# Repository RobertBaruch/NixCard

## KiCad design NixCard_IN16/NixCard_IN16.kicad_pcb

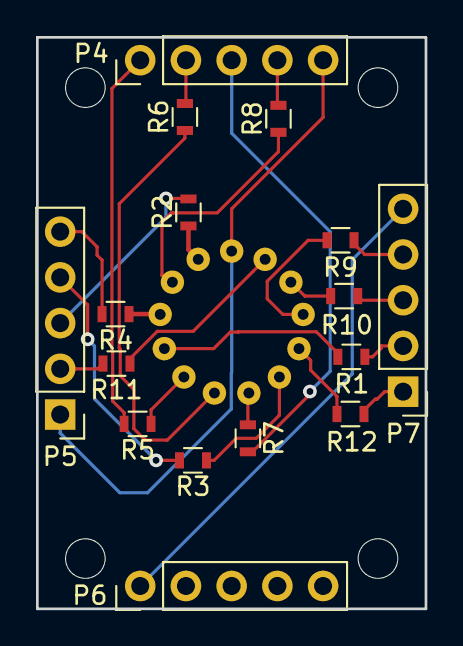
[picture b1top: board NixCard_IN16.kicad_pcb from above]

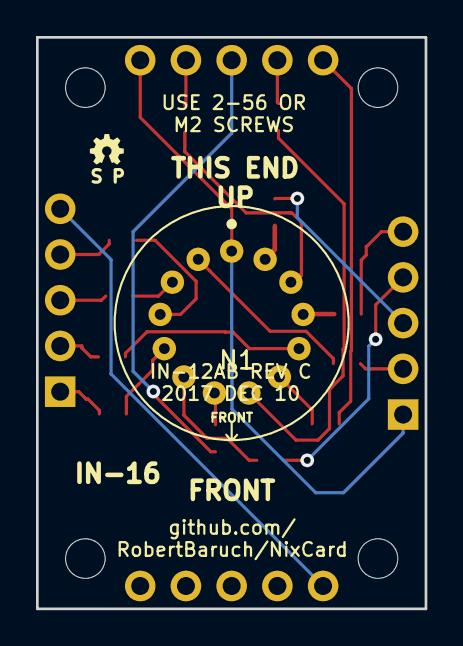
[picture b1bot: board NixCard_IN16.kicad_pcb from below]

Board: 2 copper layers, 21.6 x 31.8 mm, 18 parts (2 on the bottom side), 26 nets.

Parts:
N1: IN-16; IN-16-skt
P4, P5, P6, P7: CONN_01X05; Pin_Header_Straight_1x05_Pitch2.54mm
R1, R12: 120k; R_0603
R2, R3, R4, R5, R6, R7, R8, R9, R10, R11: 20k; R_0603
svg2mod: G***; oshw-logo-gear

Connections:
/HV0: P5.2, R11.2
/HV1: P5.3, R2.2
/HV2: P5.4, R3.2
/HV3: P5.5, R4.2
/HV4: P4.1, R5.2
/HV5: P4.2, R6.2
/HV6: P4.3, R7.2
/HV7: P4.4, R8.2
/HV8: P7.4, R9.2
/HV9: P7.3, R10.2
/HV10: P7.2, R1.2
/HV11: P7.1, R12.2
GNDREF: P6.1, P7.5
unnamed: N1.2, R2.1
unnamed: N1.3, R8.1
unnamed: N1.4, R4.1
unnamed: N1.5, R1.1
unnamed: N1.6, R5.1
unnamed: N1.7, R6.1
unnamed: N1.8, R7.1
unnamed: N1.9, R3.1
unnamed: N1.10, R12.1
unnamed: N1.11, R9.1
unnamed: N1.12, R10.1
unnamed: N1.13, R11.1
VAA: N1.1, P4.5, P5.1

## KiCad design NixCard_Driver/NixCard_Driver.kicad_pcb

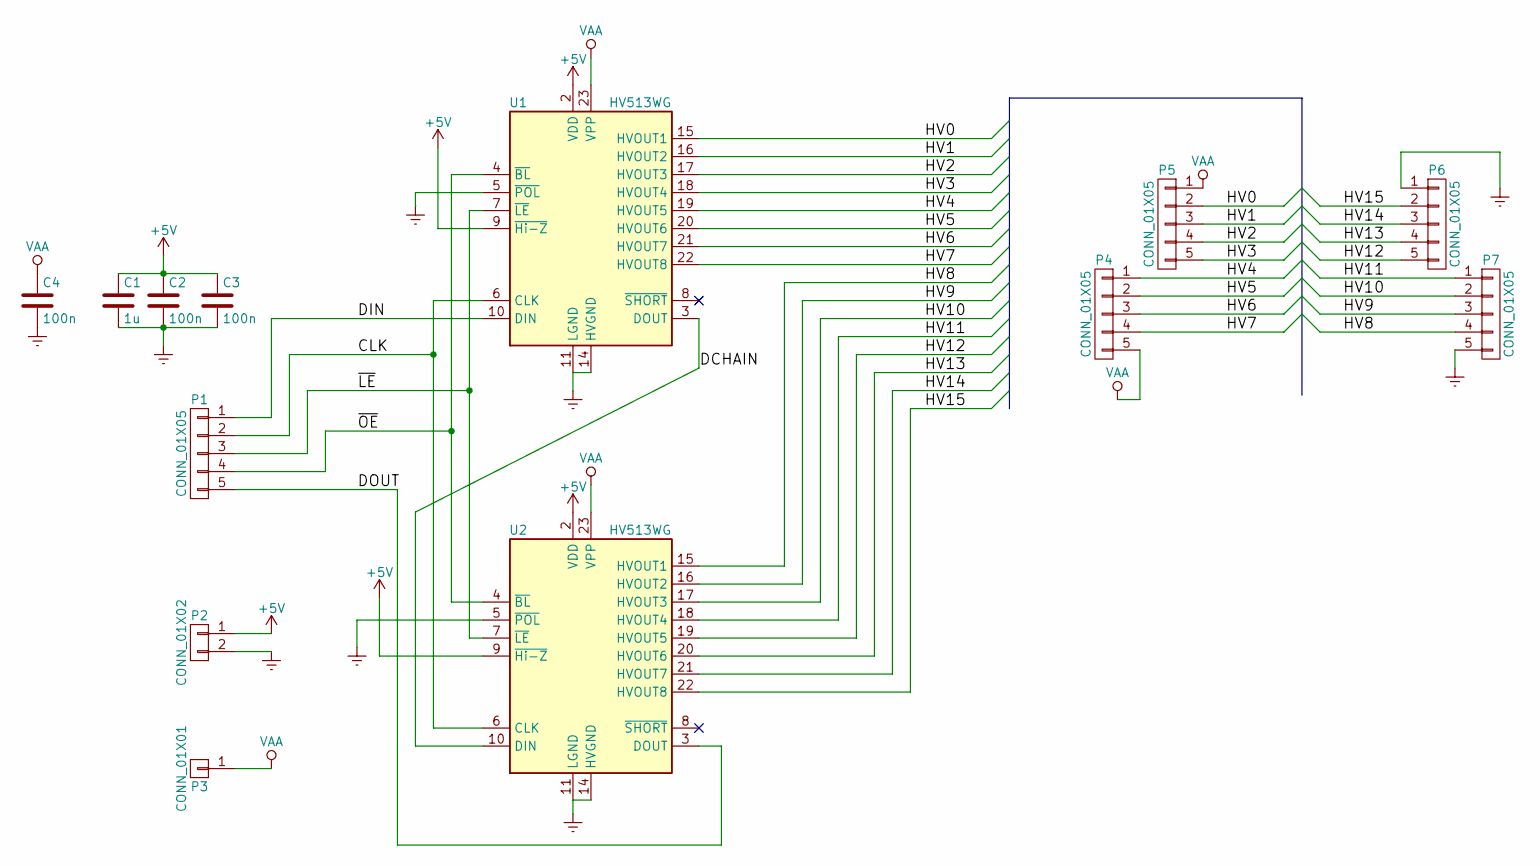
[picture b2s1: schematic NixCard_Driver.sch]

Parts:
C1: 1u; C_0603; MFG P/N C2012X5R1E105M085AC
C2, C3: 100n; C_0603; MFG P/N CGJ4J2X7R1E104K125AA
C4: 100n; C_0805; MFG P/N CGJ4J2X7R1E104K125AA
P1, P4, P5, P6, P7: CONN_01X05; PinHeader_1x05_P2.54mm_Vertical
P2: CONN_01X02; PinHeader_1x02_P2.54mm_Vertical
P3: CONN_01X01; PinHeader_1x01_P2.54mm_Vertical
U1, U2: HV513WG; SOIC-24W_7.5x15.4mm_P1.27mm; MFG P/N HV513WG

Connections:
+5V: C1.1, C2.1, C3.1, P2.1, U1.2 (VDD), U1.9 (~Hi-Z), U2.2 (VDD), U2.9 (~Hi-Z)
/CLK: P1.2, U1.6 (CLK), U2.6 (CLK)
/DCHAIN: U1.3 (DOUT), U2.10 (DIN)
/DIN: P1.1, U1.10 (DIN)
/DOUT: P1.5, U2.3 (DOUT)
/HV0: P5.2, U1.15 (HVOUT1)
/HV1: P5.3, U1.16 (HVOUT2)
/HV2: P5.4, U1.17 (HVOUT3)
/HV3: P5.5, U1.18 (HVOUT4)
/HV4: P4.1, U1.19 (HVOUT5)
/HV5: P4.2, U1.20 (HVOUT6)
/HV6: P4.3, U1.21 (HVOUT7)
/HV7: P4.4, U1.22 (HVOUT8)
/HV8: P7.4, U2.15 (HVOUT1)
/HV9: P7.3, U2.16 (HVOUT2)
/HV10: P7.2, U2.17 (HVOUT3)
/HV11: P7.1, U2.18 (HVOUT4)
/HV12: P6.5, U2.19 (HVOUT5)
/HV13: P6.4, U2.20 (HVOUT6)
/HV14: P6.3, U2.21 (HVOUT7)
/HV15: P6.2, U2.22 (HVOUT8)
/~LE: P1.3, U1.7 (~LE), U2.7 (~LE)
/~OE: P1.4, U1.4 (~BL), U2.4 (~BL)
GNDREF: C1.2, C2.2, C3.2, C4.2, P2.2, P6.1, P7.5, U1.5 (~POL), U1.11 (LGND), U1.13 (HVGND), U1.14 (HVGND), U2.5 (~POL), U2.11 (LGND), U2.13 (HVGND), U2.14 (HVGND)
VAA: C4.1, P3.1, P4.5, P5.1, U1.23 (VPP), U1.24 (VPP), U2.23 (VPP), U2.24 (VPP)

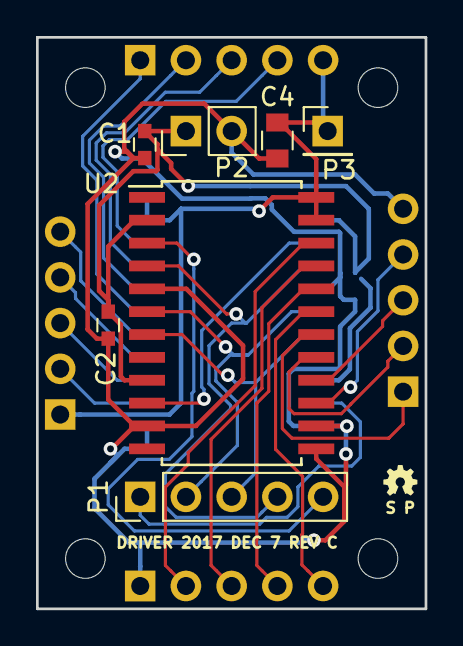
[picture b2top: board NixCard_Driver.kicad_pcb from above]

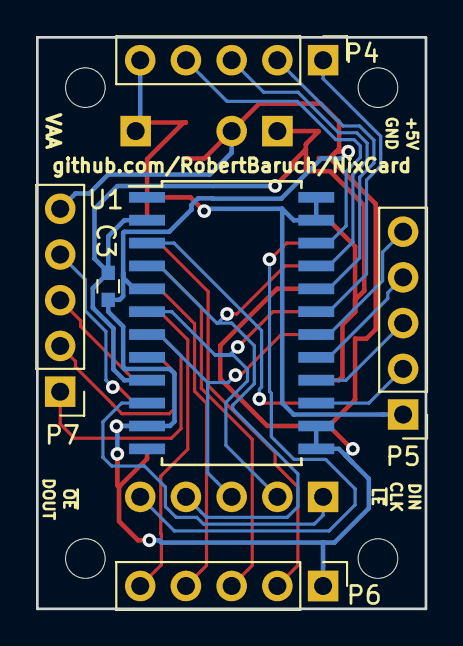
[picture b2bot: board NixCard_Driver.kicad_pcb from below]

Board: 2 copper layers, 21.6 x 31.8 mm, 14 parts (6 on the bottom side), 25 nets.

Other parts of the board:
svg2mod: G***; oshw-logo-gear

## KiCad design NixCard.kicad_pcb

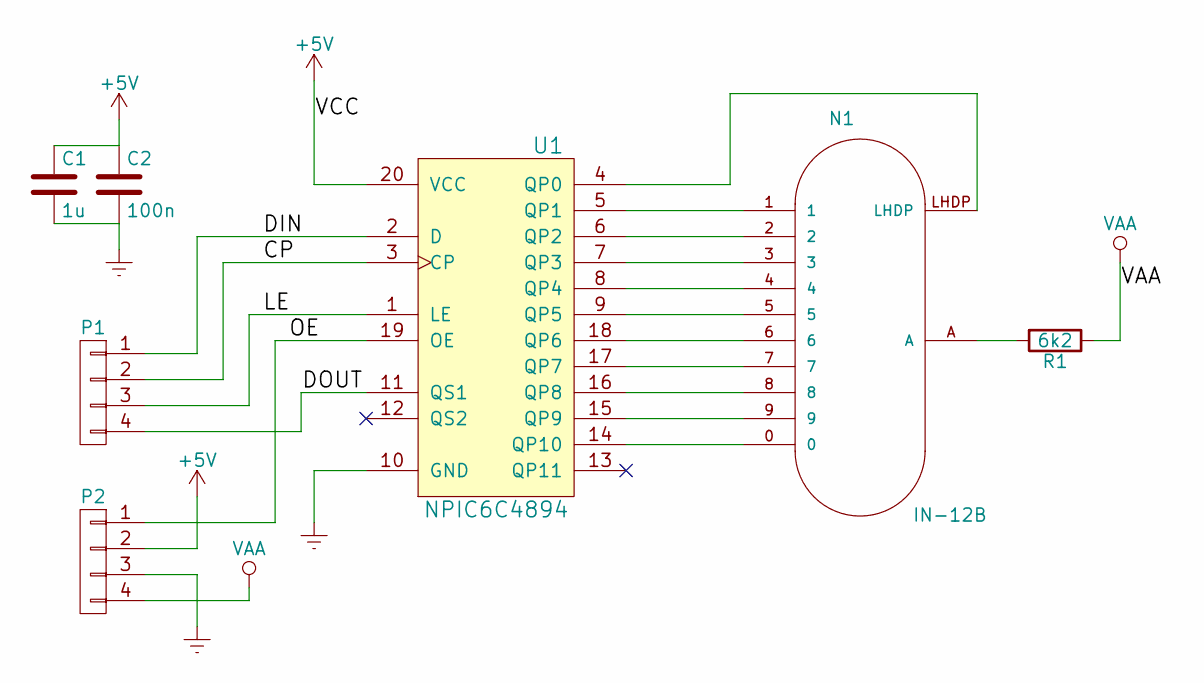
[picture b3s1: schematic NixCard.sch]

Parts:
C1: 1u; C_0805; MFG P/N C2012X5R1E105M085AC
C2: 100n; C_0805; MFG P/N CGJ4J2X7R1E104K125AA
N1: IN-12B; IN-12B-skt; MFG P/N IN-12B
P1, P2: TSW-104-07-F-S; Pin_Header_Straight_1x04; MFG P/N TSW-104-07-F-S
R1: 6k2; R_0805; MFG P/N RC0805FR-076K2L
U1: NPIC6C4894; TSSOP-20_4.4x6.5mm_Pitch0.65mm; MFG P/N NPIC6C4894PW-Q100J

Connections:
+5V: C1.1, C2.1, P2.2, U1.20 (VCC)
/CP: P1.2, U1.3 (CP)
/DIN: P1.1, U1.2 (D)
/DOUT: P1.4, U1.11 (QS1)
/LE: P1.3, U1.1 (LE)
/OE: P2.1, U1.19 (OE)
GNDREF: C1.2, C2.2, P2.3, U1.10 (GND)
unnamed: N1.0, U1.14 (QP10)
unnamed: N1.1, U1.5 (QP1)
unnamed: N1.2, U1.6 (QP2)
unnamed: N1.3, U1.7 (QP3)
unnamed: N1.4, U1.8 (QP4)
unnamed: N1.5, U1.9 (QP5)
unnamed: N1.6, U1.18 (QP6)
unnamed: N1.7, U1.17 (QP7)
unnamed: N1.8, U1.16 (QP8)
unnamed: N1.9, U1.15 (QP9)
unnamed: N1.A, R1.2
unnamed: N1.LHDP, U1.4 (QP0)
VAA: P2.4, R1.1

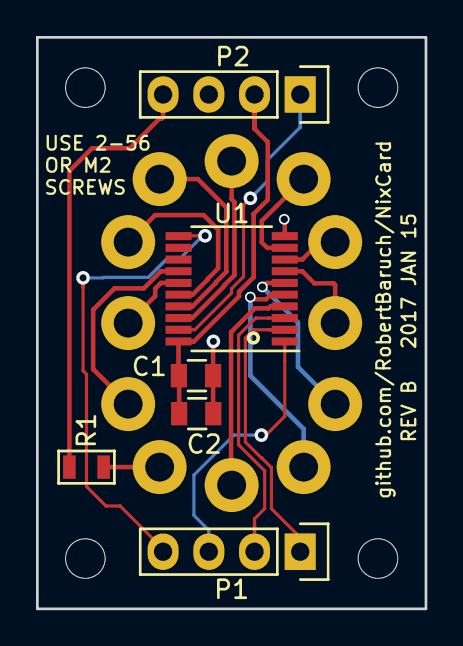
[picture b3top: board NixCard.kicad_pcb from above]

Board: 2 copper layers, 21.6 x 31.8 mm, 7 parts (1 on the bottom side), 20 nets.

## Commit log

2016-12-25 :circus_tent: Added .gitattributes & .gitignore files
2016-12-25 Rev A commit
2016-12-25 Update PCB
2017-01-09 Adds example Arduino sketch
2017-01-24 Updated PCB
2017-01-24 Updated comments in Arduino sketch
2017-12-08 Changes to two boards (driver, adapter) and HV513
2017-12-08 Corrects names (driver <-> IN12AB)
2017-12-08 Redo of driver board
2017-12-11 Initial IN-12AB board, gerbers
2017-12-11 Remove old gerbers
2017-12-11 Remove old gerber zips, add new gerber zips
2018-01-11 tiny update
2018-02-12 Adds card for IN16 (tentative, not tested)
2018-02-12 Adds xrp/usd example
